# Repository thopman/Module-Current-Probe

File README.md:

# Module-Current-Probe
Simple current probe pcb for use with eurorack and motm synthesizer modules. 

Makes it easy to place a current meter in series with power headers. Also makes it easy to power a module with a current-limited lab power-supply. Make sure to jump any power rails which are not in use for measurement. 

Currently there are 2 versions. V1 - for eurorack modules only and V2 - for eurorack and motm modules.

V1

BOM - V1 

2 x shrouded 2x8 2.54mm pin header

1 x unshrouded 2x8 2.54mm pin header

7 x 4 mm banana jack

5 x 2.54mm jumpers

optional 4 x M3 standoff (+ m3 screws or nuts)

V2

BOM - V2 

2 x shrouded 2x8 2.54mm pin header

2 x 4 pin MTA-156 pin header

1 x unshrouded 2x8 2.54mm pin header

7 x 4 mm banana jack

5 x 2.54mm jumpers

optional 4 x M3 standoff (+ m3 screws or nuts)

<----------------------------------------------------------------------------------------------------------------------------->

Copyright (c) 2016 Thomas Hopman

This documentation describes Open Hardware and is licensed under the
CERN OHL v. 1.2.
You may redistribute and modify this documentation under the terms of the
CERN OHL v.1.2. (http://ohwr.org/cernohl). This documentation is distributed
WITHOUT ANY EXPRESS OR IMPLIED WARRANTY, INCLUDING OF
MERCHANTABILITY, SATISFACTORY QUALITY AND FITNESS FOR A
PARTICULAR PURPOSE. Please see the CERN OHL v.1.2 for applicable
conditions

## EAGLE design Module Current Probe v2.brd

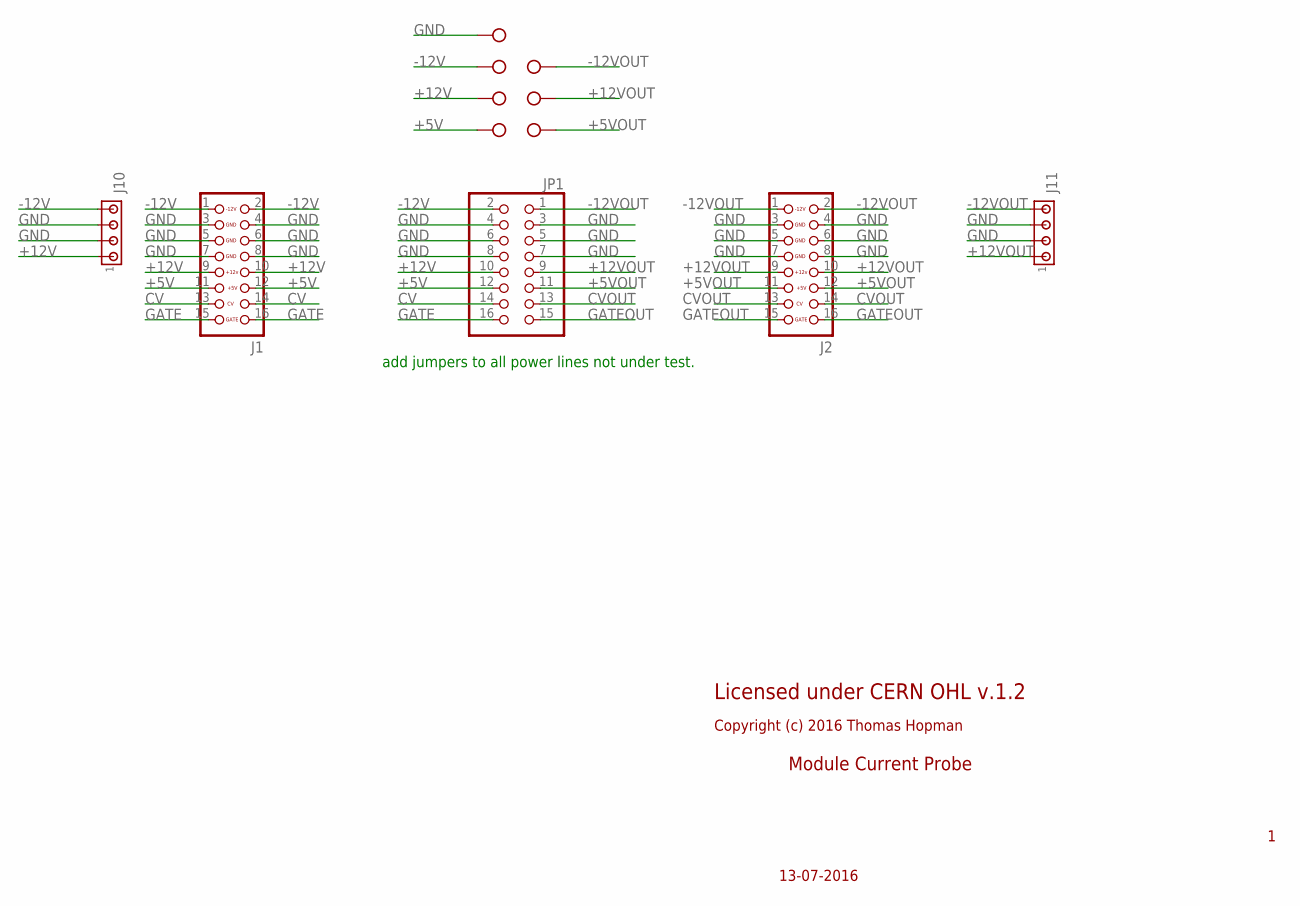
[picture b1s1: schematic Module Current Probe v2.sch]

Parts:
J1, J2: CON_HEADER_2X08-PTH-SHROUDED; PINSHRD_PTH_2X08
J3, J4, J5, J6, J7, J8, J9: BANANA-JACK; BANANA-PRINT
J10, J11: MTA04-156; 1X4MTA
JP1: PINHD-2X8; 2X08

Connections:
+5V: J1.11, J1.12, J5.P$1, JP1.12
+5VOUT: J2.11, J2.12, J8.P$1, JP1.11
+12V: J1.9, J1.10, J4.P$1, J10.1, JP1.10
+12VOUT: J2.9, J2.10, J7.P$1, J11.1, JP1.9
-12V: J1.1, J1.2, J3.P$1, J10.4, JP1.2
-12VOUT: J2.1, J2.2, J6.P$1, J11.4, JP1.1
CV: J1.13, J1.14, JP1.14
CVOUT: J2.13, J2.14, JP1.13
GATE: J1.15, J1.16, JP1.16
GATEOUT: J2.15, J2.16, JP1.15
GND: J1.3, J1.4, J1.5, J1.6, J1.7, J1.8, J2.3, J2.4, J2.5, J2.6, J2.7, J2.8, J9.P$1, J10.2, J10.3, J11.2, J11.3, JP1.3, JP1.4, JP1.5, JP1.6, JP1.7, JP1.8

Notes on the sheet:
add jumpers to all power lines not under test.
13-07-2016
Module Current Probe
Licensed under CERN OHL v.1.2
Copyright (c) 2016 Thomas Hopman

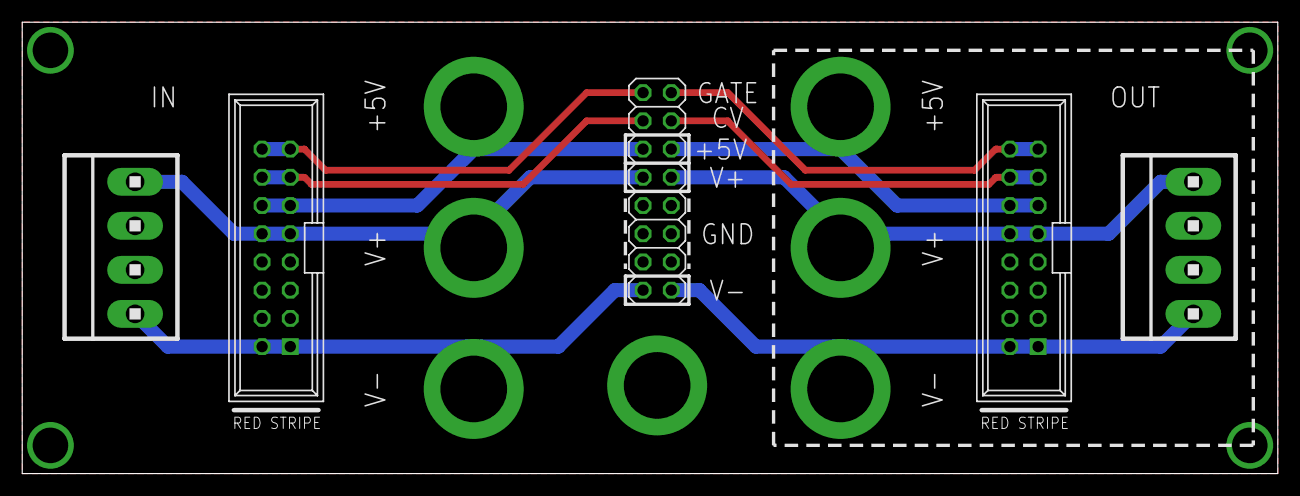
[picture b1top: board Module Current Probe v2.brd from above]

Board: 2 copper layers, 113.0 x 40.6 mm, 12 parts (0 on the bottom side), 11 nets.

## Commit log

2016-07-13 Added design files, pdf renders and cern ohl v1.2 files.
2016-07-13 Update README.md
    added a image to readme
2016-07-13 Update README.md
    changed image to updated version
2016-07-13 Added ground connection for connecting a lab power supply.
2016-07-20 Added V2 version with support for MOTM modules.
2016-07-20 Update README.md
    added BOM
2016-07-20 Update README.md
    updated BOM
2017-06-26 update text to make the procedure more clear
    update text to make the procedure more clear

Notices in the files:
Module Current Probe v2.brd:
Copyright 2016 Thomas Hopman
